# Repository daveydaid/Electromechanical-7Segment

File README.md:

# Electromechanical-7Segment

# Detailed Blog Post: 

[https://davidmcdaid.wordpress.com/2022/03/08/electromechanical-7-segment-display/](https://davidmcdaid.wordpress.com/2022/03/08/electromechanical-7-segment-display/)

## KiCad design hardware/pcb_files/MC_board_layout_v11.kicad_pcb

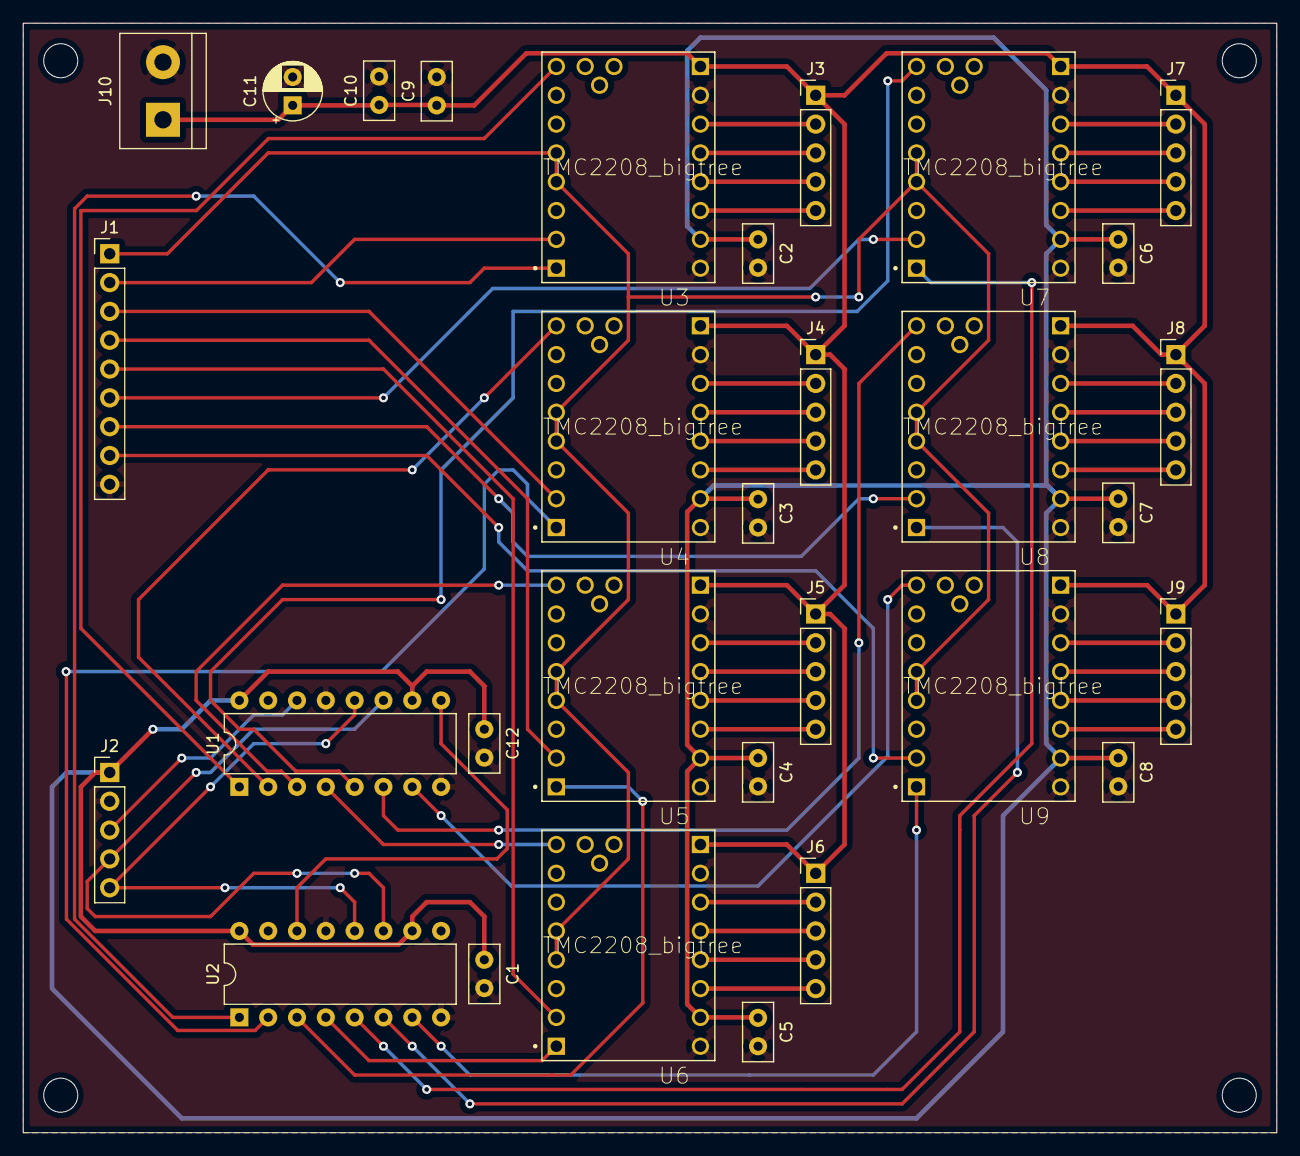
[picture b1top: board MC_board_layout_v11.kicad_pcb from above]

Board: 2 copper layers, 110.5 x 97.8 mm, 31 parts (0 on the bottom side), 57 nets.

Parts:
C1, C2, C3, C4, C5, C6, C7, C8, C9, C10, C12: 0.1uF; C_Disc_D5.0mm_W2.5mm_P2.50mm
C11: 100uF; CP_Radial_D5.0mm_P2.50mm
J1: Conn_01x09; PinHeader_1x09_P2.54mm_Vertical
J2: Conn_01x05; PinHeader_1x05_P2.54mm_Vertical
J3, J4, J5, J6, J7, J8, J9: Screw_Terminal_01x05; PinHeader_1x05_P2.54mm_Vertical
J10: Screw_Terminal_01x02; TerminalBlock_bornier-2_P5.08mm
U1, U2: 74HC595; DIP-16_W7.62mm
U3, U4, U5, U6, U7, U8, U9: TMC2208_bigtree; TMC2208_SILENTSTEPSTICK_UPDATE

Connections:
GNDREF: C1.2, C2.2, C3.2, C4.2, C5.2, C6.2, C7.2, C8.2, C9.2, C10.2, C11.2, C12.2, J1.9, J2.2, J10.2, U1.8, U1.13, U2.8, U2.13, U3.1, U3.7, U4.1, U4.7, U5.1, U5.7, U6.1, U6.7, U7.1, U7.7, U8.1, U8.7, U9.1, U9.7
unnamed: C9.1, C10.1, C11.1, J3.1, J4.1, J5.1, J6.1, J7.1, J8.1, J9.1, J10.1, U3.8, U4.8, U5.8, U6.8, U7.8, U8.8, U9.8
unnamed: J1.1, U3.12, U3.13, U4.12, U4.13, U5.12, U5.13, U6.12, U6.13, U7.12, U7.13, U8.12, U8.13, U9.12, U9.13
unnamed: J1.2, U3.10
unnamed: J1.3, U4.10
unnamed: J1.4, U5.10
unnamed: J1.5, U6.10
unnamed: J1.6, U7.10
unnamed: J1.7, U8.10
unnamed: J1.8, U9.10
unnamed: J2.3, U1.14
unnamed: J2.4, U1.11, U2.11
unnamed: J2.5, U1.12, U2.12
unnamed: J3.2, U3.6
unnamed: J3.3, U3.5
unnamed: J3.4, U3.4
unnamed: J3.5, U3.3
unnamed: J4.2, U4.6
unnamed: J4.3, U4.5
unnamed: J4.4, U4.4
unnamed: J4.5, U4.3
unnamed: J5.2, U5.6
unnamed: J5.3, U5.5
unnamed: J5.4, U5.4
unnamed: J5.5, U5.3
unnamed: J6.2, U6.6
unnamed: J6.3, U6.5
unnamed: J6.4, U6.4
unnamed: J6.5, U6.3
unnamed: J7.2, U7.6
unnamed: J7.3, U7.5
unnamed: J7.4, U7.4
unnamed: J7.5, U7.3
unnamed: J8.2, U8.6
unnamed: J8.3, U8.5
unnamed: J8.4, U8.4
unnamed: J8.5, U8.3
unnamed: J9.2, U9.6
unnamed: J9.3, U9.5
unnamed: J9.4, U9.4
unnamed: J9.5, U9.3
unnamed: U1.1, U3.16
unnamed: U1.2, U4.16
unnamed: U1.3, U5.16
unnamed: U1.4, U6.16
unnamed: U1.5, U7.16
unnamed: U1.6, U8.16
unnamed: U1.7, U9.16
unnamed: U1.9, U2.14
unnamed: U2.1, U3.9
unnamed: U2.2, U4.9
unnamed: U2.3, U5.9
unnamed: U2.4, U6.9
unnamed: U2.5, U7.9
unnamed: U2.6, U8.9
unnamed: U2.7, U9.9
VCC: C1.1, C2.1, C3.1, C4.1, C5.1, C6.1, C7.1, C8.1, C12.1, J2.1, U1.10, U1.16, U2.10, U2.16, U3.2, U4.2, U5.2, U6.2, U7.2, U8.2, U9.2

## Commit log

2022-02-21 Initial git post
    Moving from local machine to git from 21/02/2022
2022-02-22 Directory restructure
    Just moving files into separate folders
2022-02-24 Removing TODOs
    Removed some TODOs throughout main source file. Also added basic header descriptions
2022-03-02 v3.7 Updates
    + new header for pin defines
    + new ISR for LED strip control
    ~ removed version number from .ino file
    ~ fixed formatting in all headers
2022-03-02 v3.7.1 Updates
    + added LED_GATE_CONTROL define
    ~ replaced hard-coded numbers throughout
2022-03-04 v3.7.2 Updates
    - Removing some TODOs
    - Fixing small formatting issues
2022-03-14 Adding hardware files
    + All 3D files
    + schematics
    + pcb layout
2022-03-15 Create LICENSE
